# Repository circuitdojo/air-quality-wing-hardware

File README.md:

# Air Quality Wing Hardware

## What is it?

The Air Quality Wing, designed by [Jared Wolff](https://www.jaredwolff.com) aka Circuit Dojo, is an all-in-one air quality sensor for Feather based development boards. It brings together a trio of sensors to give you as many data points as possible. That way, there won’t be anything missing when you go to measure the air inside your home or workplace.

Here’s what’s on board:

### Particulate Sensing

The Air Quality Wing also has support for the **Honeywell HPMA115S0 dust sensor**. This sensor counts the concentration of potentially harmful particulates in the air. Plus, it does it all using ***lasers.***

It can detect both large particles 10µm in diameter and smaller ones less than 2.5µm in diameter. These are the same readings that are commonly known as PM10 and PM2.5.

### Sensing Volatile Compounds

Second to that, is the **Sensirion SGP40**. This senses volatile organic compounds and eC02. These types of readings are useful in places where there may be combustion. (Think stoves, furnaces, etc) It can act as an early warning mechanism. That way you stay safe, happy and healthy!

### Temperature and Humidity

Finally, the **Sensirion SHTC** temperature and humidity sensor. These readings can be used on their own. Additionally they’re used by the SGP40 to compute an accurate TVOC.

### Flexible Power Sources

No outlet nearby where you want to measure? No problem!

You can easily plug in almost any lithium polymer battery to your Feather based board and use it immediately. The Air Quality Wing has extra circuitry that allow you to use either USB or battery power. How great is that?

[To get yours go here.](https://www.jaredwolff.com/store/air-quality-wing/)

## Library/Code

Here is is the links for the [Zephyr example code](https://github.com/circuitdojo/air-quality-wing-zephyr-demo). Here's the [Rust code](https://github.com/circuitdojo/air-quality-wing-rust-demo). The Rust code is a work in progress.

## Changelog

## v6 - (October 2021)

**Changed:**

* Formfactor to standard Feather size
* Replaced temperature/humidity sensor with SHTC3
* Replaced TVOC sensor with SGP40
* Changed MCP1640 package to DSON from SOT23-5
* Hatched ground planes on both top and bottom
* Re-designed sensor placement
* Thermal isolation slots for SHTC3
* Pinout for PM2.5 connector reverted back to original design (allows for bidirectional use of cable)

**Added:**

* Added I2C power control to D4
* Added battery backpack (CR2 holder)

## v4

- Relocated the Si7021 to a separate "lily pad" for heat isolation

## v3

- Fixed bug related supply voltage not being stable to the HPMTA115S0
- Relocated D7 to D5 for CCS811 reset signal
- Changed connector pinout. That way the cable does't have to be twisted.

## v2

- Added ferrite to shunt noise
- Swapped out MCP1624 with MCP1640

## License

Hardware released under the CERN Open Hardware Licence Version 2 - Weakly Reciprocal. See **LICENSE** for more info.

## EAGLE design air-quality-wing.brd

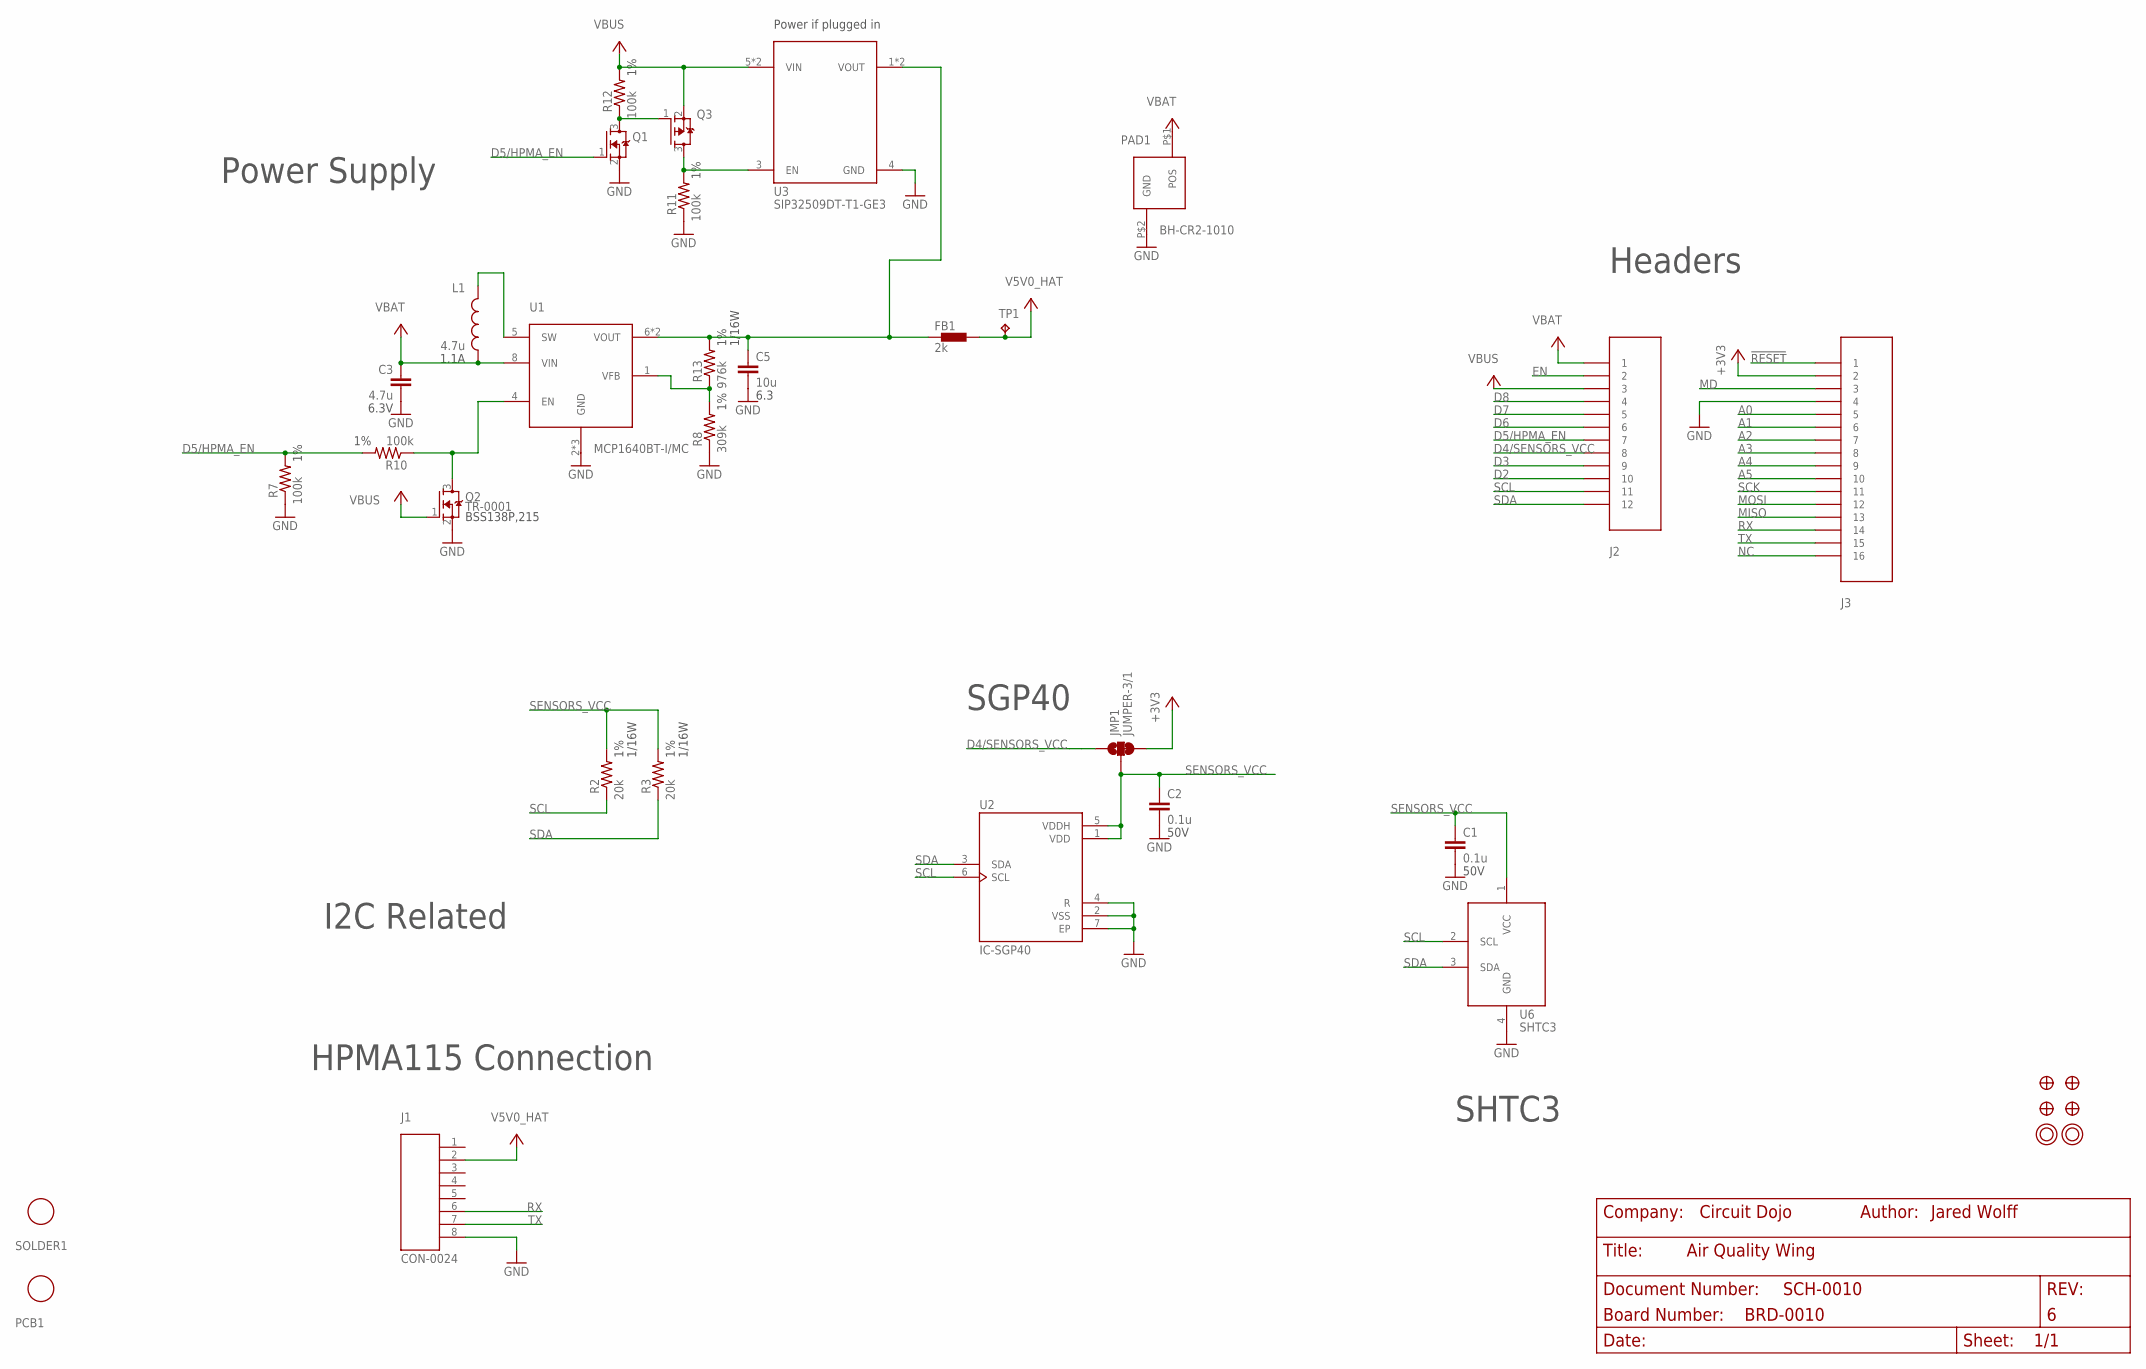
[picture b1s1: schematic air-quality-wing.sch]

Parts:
C1, C2: 0.1u; CAPC1005X55N
C3: 4.7u; C0603
C5: 10u; C0603
FB1: 2k; R0805
J1: CON-0024; 0532610871
J2: CON-HEADER-1X12-PPPC121LFBN-RC; CON-HEADER-1X12
J3: CON-HEADER-1X16-PPPC161LFBN-RC; CON-HEADER-1X16
JMP1: JUMPER-3/1; JUMPER-ROUND-3-NO-R
L1: 4.7u; IND-2P0X2P0X1P2
PAD1: BH-CR2-1010; 1010
PCB1: PCB-PS-AQW; PLACEHOLDER
Q1, Q2: TR-0001; SOT23
Q3: TR-0003; SOT23@1
R2, R3: 20k; R0402-M
R7, R10, R11, R12: 100k; R0402-M
R8: 309k; R0402-M
R13: 976k; R0402-M
SOLDER1: SOLDER; PLACEHOLDER
TP1: TP; TP-1P27
U1: POWER-VREG-FB-EN-SW-350MA-DFN8; DFN200X300X100-9N
U2: IC-SGP40; XDCR_SGP30-2.5K
U3: POWER-SWITCH-SIP32509-SO23-6; SOT23-6
U6: IC-SHTC3
U$3, U$4, U$34, U$35: FIDUCIAL-1MM
U$31, U$32: MOUNTING-HOLE-2.5MM-PLATED

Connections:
!RESET: J3.1
+3V3: J3.2, JMP1.P$3 (3)
A0: J3.5
A1: J3.6
A2: J3.7
A3: J3.8
A4: J3.9
A5: J3.10
D2: J2.10
D3: J2.9
D4/SENSORS_VCC: J2.8, JMP1.P$1 (1)
D5/HPMA_EN: J2.7, Q1.1 (G), R7.2, R10.2
D6: J2.6
D7: J2.5
D8: J2.4
EN: J2.2
GND: C1.2, C2.2, C3.2, C5.2, J1.8, J3.4, PAD1.P$2 (GND), Q1.2 (S), Q2.2 (S), R7.1, R8.1, R11.1, U1.2 (GND), U1.3 (GND), U1.9 (GND), U2.2 (VSS), U2.4 (R), U2.7 (EP), U3.4 (GND), U6.4 (GND)
LOAD_SW_EN: Q3.3 (D), R11.2, U3.3 (EN)
MD: J3.3
MISO: J3.13
MOSI: J3.12
unnamed: R8.2, R13.1, U1.1 (VFB)
NC: J3.16
Q1_D: Q1.3 (D), Q3.1 (G), R12.1
RX: J1.6, J3.14
SCK: J3.11
SCL: J2.11, R2.1, U2.6 (SCL), U6.2 (SCL)
SDA: J2.12, R3.1, U2.3 (SDA), U6.3 (SDA)
SENSORS_VCC: C1.1, C2.1, JMP1.P$2 (2), R2.2, R3.2, U2.1 (VDD), U2.5 (VDDH), U6.1 (VCC)
TX: J1.7, J3.15
V5V0_BEAD: C5.1, FB1.1, R13.2, U1.6 (VOUT), U1.7 (VOUT), U3.1 (VOUT), U3.2 (VOUT)
V5V0_EN: Q2.3 (D), R10.1, U1.4 (EN)
V5V0_HAT: FB1.2, J1.2, TP1.P$1, TP1.P$2, TP1.TP
V5V0_SW: L1.P$1 (1), U1.5 (SW)
VBAT: C3.1, J2.1, L1.P$2 (2), PAD1.P$1 (POS), U1.8 (VIN)
VBUS: J2.3, Q2.1 (G), Q3.2 (S), R12.2, U3.5 (VIN), U3.6 (VIN)

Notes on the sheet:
Power Supply
SHTC3
SGP40
HPMA115 Connection
Headers
Power if plugged in
I2C Related

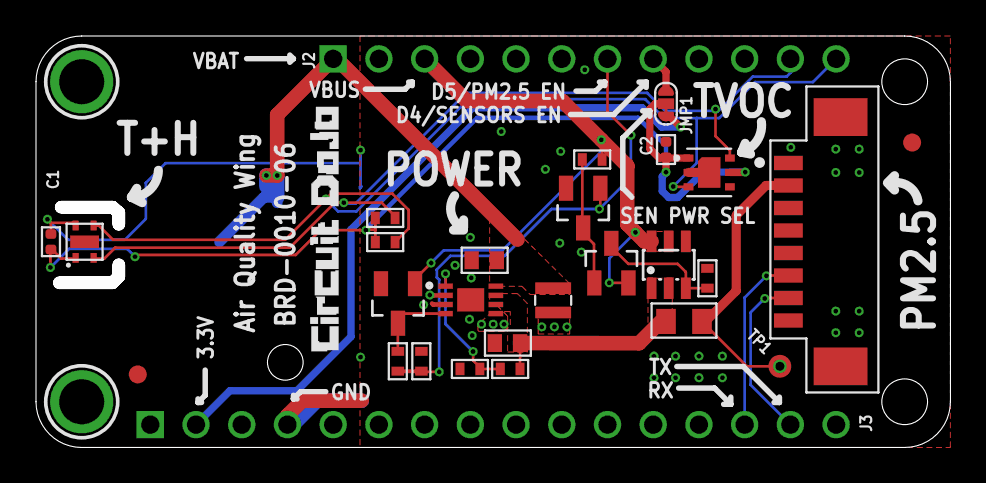
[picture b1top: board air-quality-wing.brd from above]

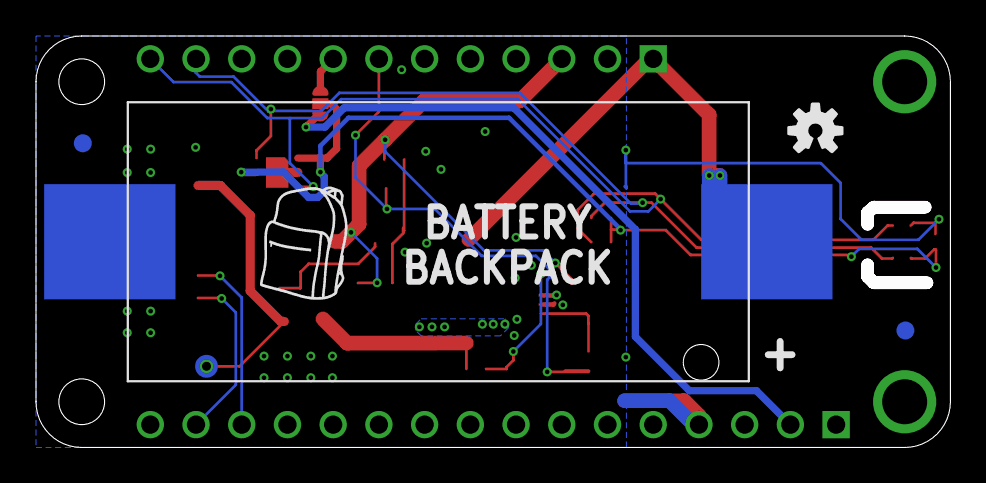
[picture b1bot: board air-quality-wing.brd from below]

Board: 2 copper layers, 50.1 x 22.2 mm, 39 parts (5 on the bottom side), 18 nets.

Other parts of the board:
U$1: OSHW-LOGO-S
U$2: LOGO-CIRCUITDOJO
U$5: BACKPACK
U$6: A3L-LOC

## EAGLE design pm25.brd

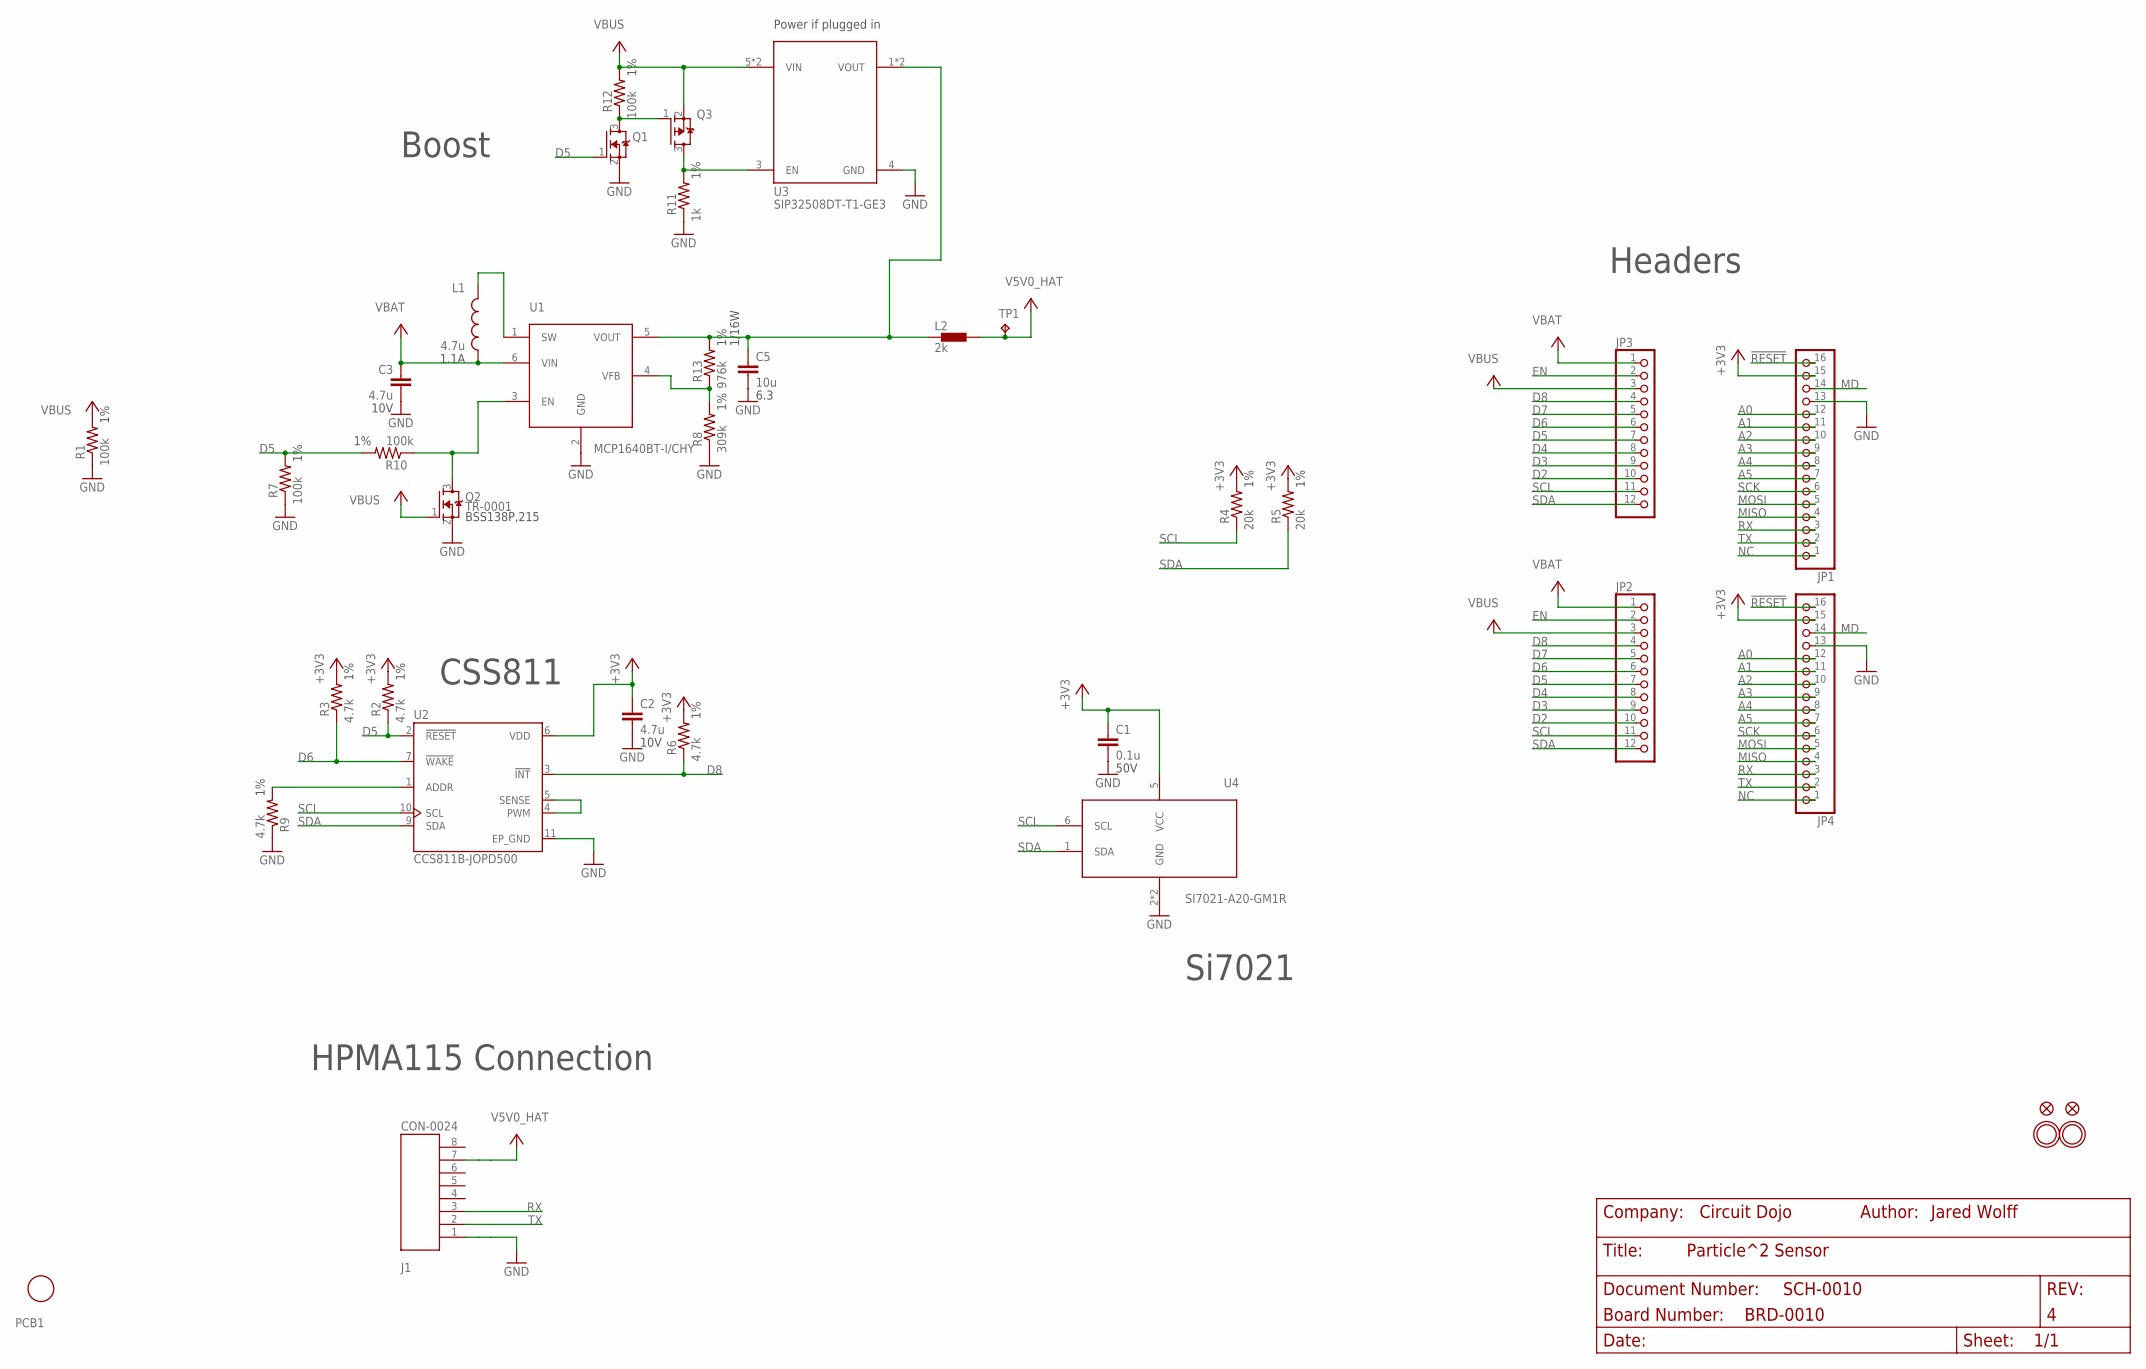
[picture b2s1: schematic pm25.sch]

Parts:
C1: 0.1u; CAPC1005X55N
C2, C3: 4.7u; C0603
C5: 10u; C0603
J1: CON-0024; 0532610871
JP1: HEADER-1X16ROUND; 1X16_ROUND; MPN PPPC161LFBN-RC
JP2: HEADER-1X12; 1X12_ROUND
JP3: HEADER-1X12; 1X12_ROUND; MPN PPPC121LFBN-RC
JP4: HEADER-1X16ROUND; 1X16_ROUND
L1: 4.7u; IND-2P0X2P0X1P2
L2: 2k; R0805
PCB1: PCB-PS-CCS811-SI7021; PLACEHOLDER
Q1, Q2: TR-0001; SOT23
Q3: TR-0003; SOT23
R1, R7, R10, R12: 100k; R0402
R2, R3, R6, R9: 4.7k; R0402
R4, R5: 20k; R0402
R8: 309k; R0402
R11: 1k; R0402
R13: 976k; R0402
TP1: TP; TP-1P27
U1: POWER-VREG-FB-EN-SW-350MA; SOT23-6
U2: CCS811B-JOPD500; SON60P400X270X110-11N
U3: POWER-SWITCH-SIP32508-SO23-6; SOT23-6
U4: SI7021-A20-GM1R; SON100P300X300X80-7N
U$31, U$32: MOUNTINGHOLE2.5; MOUNTINGHOLE_2.5_PLATED
U$34, U$35: FIDUCIAL""; FIDUCIAL_1MM

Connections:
!RESET: JP1.16, JP4.16
+3V3: C1.1, C2.1, JP1.15, JP4.15, R2.2, R3.2, R4.2, R5.2, R6.2, U2.6 (VDD), U4.5 (VCC)
A0: JP1.12, JP4.12
A1: JP1.11, JP4.11
A2: JP1.10, JP4.10
A3: JP1.9, JP4.9
A4: JP1.8, JP4.8
A5: JP1.7, JP4.7
D2: JP2.10, JP3.10
D3: JP2.9, JP3.9
D4: JP2.8, JP3.8
D5: JP2.7, JP3.7, Q1.1 (G), R2.1, R7.2, R10.2, U2.2 (!RESET)
D6: JP2.6, JP3.6, R3.1, U2.7 (!WAKE)
D7: JP2.5, JP3.5
D8: JP2.4, JP3.4, R6.1, U2.3 (!INT)
EN: JP2.2, JP3.2
GND: C1.2, C2.2, C3.2, C5.2, J1.1, JP1.13, JP4.13, Q1.2 (S), Q2.2 (S), R1.1, R7.1, R8.1, R9.1, R11.1, U1.2 (GND), U2.11 (EP_GND), U3.4 (GND), U4.2 (GND), U4.7 (GND)
MD: JP1.14, JP4.14
MISO: JP1.4, JP4.4
MOSI: JP1.5, JP4.5
unnamed: L1.P$1 (1), U1.1 (SW)
unnamed: R8.2, R13.1, U1.4 (VFB)
unnamed: Q1.3 (D), Q3.1 (G), R12.1
unnamed: R9.2, U2.1 (ADDR)
unnamed: U2.4 (PWM), U2.5 (SENSE)
unnamed: Q2.3 (D), R10.1, U1.3 (EN)
unnamed: Q3.3 (D), R11.2, U3.3 (EN)
NC: JP1.1, JP4.1
RX: J1.3, JP1.3, JP4.3
SCK: JP1.6, JP4.6
SCL: JP2.11, JP3.11, R4.1, U2.10 (SCL), U4.6 (SCL)
SDA: JP2.12, JP3.12, R5.1, U2.9 (SDA), U4.1 (SDA)
TX: J1.2, JP1.2, JP4.2
V5V0_BEAD: C5.1, L2.1, R13.2, U1.5 (VOUT), U3.1 (VOUT), U3.2 (VOUT)
V5V0_HAT: J1.7, L2.2, TP1.P$1, TP1.P$2, TP1.TP
VBAT: C3.1, JP2.1, JP3.1, L1.P$2 (2), U1.6 (VIN)
VBUS: JP2.3, JP3.3, Q2.1 (G), Q3.2 (S), R1.2, R12.2, U3.5 (VIN), U3.6 (VIN)

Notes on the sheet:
Boost
Si7021
CSS811
HPMA115 Connection
Headers
Power if plugged in

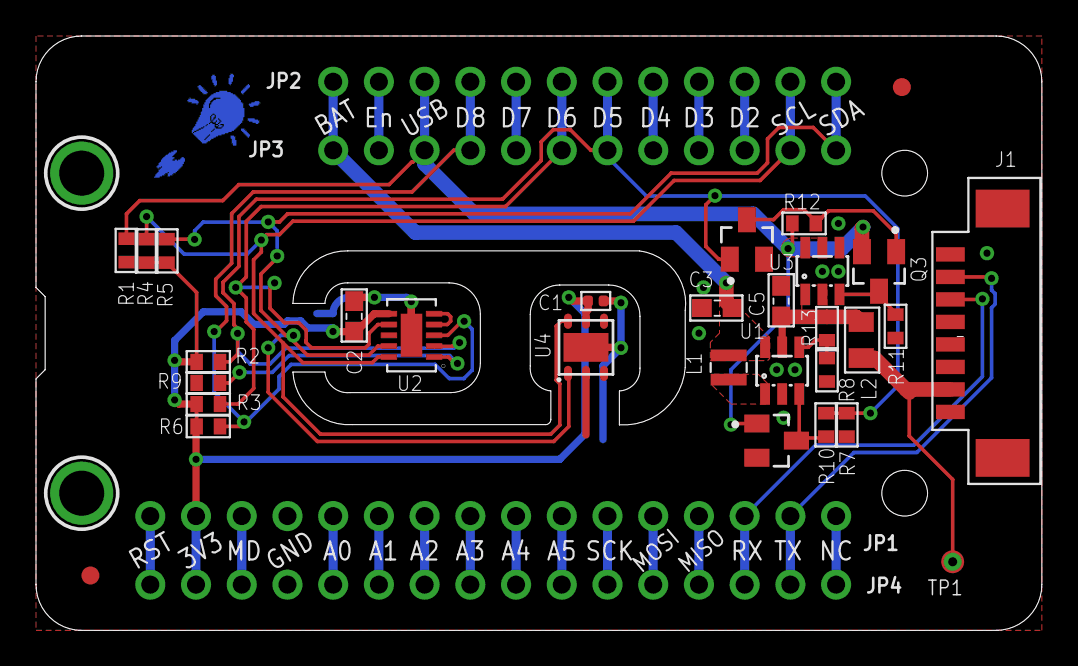
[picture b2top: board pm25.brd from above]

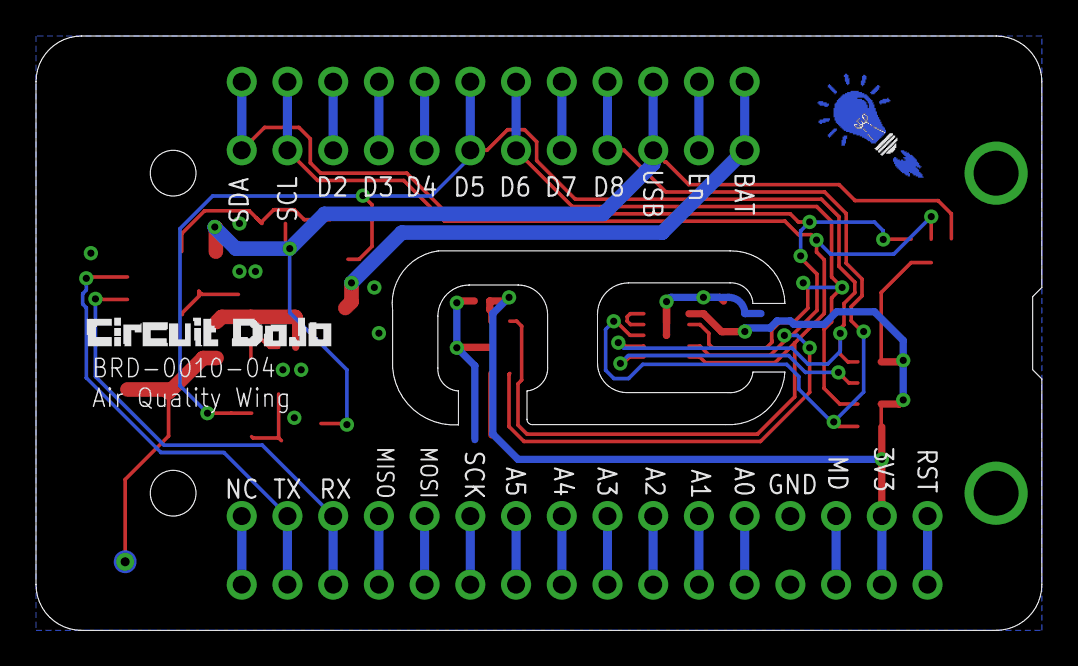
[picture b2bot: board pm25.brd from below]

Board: 2 copper layers, 55.9 x 33.0 mm, 39 parts (2 on the bottom side), 37 nets.

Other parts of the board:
U$1: LOGO-CIRCUITDOJO-BULB
U$2: LOGO-CIRCUITDOJO

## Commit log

2019-04-01 First commit.
2019-04-03 Adding license info
2019-04-03 Adjust size
2019-04-08 Adding frtizing from firmware repo.
2019-04-12 Slight hardware update. Substitute MCP1640 on U1 Add L2 Add TP1
2019-04-25 Replacing connection from D7 with D5 (so the LED isn't always on)
2019-04-25 Fixing issue with intermittent BOOST/USB control.
2019-10-11 Updating board based on recommendations
2019-10-17 Fixing load switch option
2019-10-21 Renaming to Air Quality Wing
2019-11-07 Update README.md
    Updating Readme
2019-11-07 Renaming board files and docs
2019-11-07 Adding pdf
2019-11-07 Adding rev4 schematic
2020-05-13 Create LICENSE
2021-09-23 Add files via upload
    Added:
    * Rev2 schematic.
2021-09-27 Committing v6 changes:
    Changed:
    * Formfactor to standard Feather size
    * Replaced temperature/humidity sensor with SHTC3
    * Replaced TVOC sensor with SGP40
    * Changed MCP1640 package to DSON from SOT23-5
    * Hatched ground planes on both top and bottom

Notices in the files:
parts and their libraries:
SparkFun-Aesthetics: Licensing: Creative Commons ShareAlike 4.0 International - https://creativecommons.org/licenses/by-sa/4.0
microbuilder: This work is placed in the public domain, and may be freely used for commercial and non-commercial work with the following conditions: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
